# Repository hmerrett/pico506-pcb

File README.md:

# Pico506 hardware — rev 1.0

A dedicated PCB for the Pico506 ST-506/MFM/RLL hard drive emulator: two-layer,
138 × 74 mm, all through-hole, with real card-edge tabs so it plugs into a
period ST-506 control/data cable pair the same way an ST-225 does.

**This repository is the board only.** The emulator itself — the RP2040 firmware,
the PIO signal generation, the SD card image format, and the explanation of how
any of it works — is Kuba Szczodrzyński's
[**kuba2k2/pico506**](https://github.com/kuba2k2/pico506). Read that first; this
board is useless without it. Kuba's write-up
[*Emulating a 1987 proprietary RLL hard drive*](https://kuba.szczodrzynski.pl/posts/toshiba-t1200/rll-hdd-emulator/)
is the long-form story of the project and the reference for the interface
behaviour this layout is built around.

This file covers the board: what to buy, how to strap it, and what to tell
the fab. See [Credits](#credits) for what is original here and what is not.

> **Status:** schematic and layout are complete and clean — ERC 0, DRC 0 at
> `--severity-all` (see [`erc.txt`](erc.txt), [`drc.txt`](drc.txt)).
> **It has not been fabricated or brought up yet.** Nothing here has been
> validated against real hardware; treat rev 1.0 as a first spin.

| Front | Back |
|---|---|
|  |  |

Also in [`doc/`](doc/): an isometric render, front/back layer PDFs, gerbers +
Excellon (`pico506-gerbers.zip`), a CSV BOM and a placement file. The schematic
PDF is [`pico506-sch.pdf`](pico506-sch.pdf).

## Bill of materials

36 line items, 62 parts, nothing surface-mount and nothing exotic. Quantities
and designators below are generated from the schematic — the machine-readable
copy is [`doc/pico506-bom.csv`](doc/pico506-bom.csv).

### Semiconductors

| Ref | Qty | Value | Notes |
|---|---|---|---|
| U1 | 1 | Raspberry Pi Pico | Pico or Pico W, THT header or castellated. The footprint takes either. |
| U2, U3 | 2 | 74LS05 | Hex inverter, **open collector**. Not 7404 — the open-collector output is what lets the terminated 5 V bus idle high. |
| U4, U5 | 2 | 7438 | Quad NAND, **open collector**, buffered. Plain `7438` (or `74S38`) is preferred over `74LS38`: the LS part sinks 24 mA where the bus wants 40 mA to hold a 220/330-terminated line at a valid low. 74LS38 will usually work with one drive on a short cable; use 7438 if you want spec margin. |
| U6 | 1 | AM26LS31CN | Quad RS-422 differential **driver** (READ data out). |
| U7 | 1 | MC3486N | Quad RS-422 differential **receiver** (WRITE data in). **AM26LS32AC** is a drop-in alternative and is usually easier to find. |
| Q1 | 1 | 2N3904 | LED sink for the front-panel activity LED. Any small NPN. |
| D1 | 1 | 1N5817 | Schottky, feeds the Pico's VSYS from +5 V. A 1N5819 or SS14-class part is fine; don't substitute a plain 1N400x — the forward drop leaves too little VSYS headroom. |
| D2 | 1 | LED 5 mm amber | `ACT` — activity. |
| D3 | 1 | LED 5 mm green | `PWR` — power. |

### Passives

| Ref | Qty | Value | Notes |
|---|---|---|---|
| RN1 | 1 | 220 Ω SIP-9 | Terminator pull-up half. **Bourns 4609X-101-221** (bussed, 8 resistors, common pin 1). Fit in a 9-pin SIP socket — see [Termination](#termination). |
| RN2 | 1 | 330 Ω SIP-9 | Terminator pull-down half. **Bourns 4609X-101-331**. Also socketed. |
| R21 | 1 | 220 Ω | Fixed 220/330 divider on the *selected* drive-select line, after the J4 jumper — the way an ST-225 does it. Not removable. |
| R22 | 1 | 330 Ω | ” |
| R1–R9, R16 | 10 | 1 kΩ | R1–R9 pull the 74LS05 open-collector outputs up to +3V3 for the Pico. R16 is the PWR LED resistor. |
| R10, R14, R15 | 3 | 470 Ω | R10 is the WRITE FAULT input pull-up; R14/R15 are the ACT LED resistors (on-board and front-panel). |
| R11, R12 | 2 | 100 Ω | R11 buzzer series, R12 terminates the WRITE differential pair across U7's inputs. |
| R13 | 1 | 4.7 kΩ | Q1 base. |
| R17–R20 | 4 | 10 kΩ | SD card SPI pull-ups. |
| C1 | 1 | 100 µF 16 V | Bulk on +5 V. Radial, 6.3 mm body, 2.5 mm pitch. |
| C2 | 1 | 22 µF 16 V | Bulk on VSYS. Radial, 5 mm body. |
| C3–C9 | 7 | 100 nF | Ceramic disc, 5 mm pitch. One per logic IC (C3–C8) plus one for the SD socket (C9). |
| C10 | 1 | 10 µF 16 V | +3V3 bulk next to the SD socket. |

All resistors are 1/4 W axial on a 10.16 mm (0.4 in) footprint — the classic
DIN0207 body with the leads bent out, so they lie flat.

### Connectors and mechanical

| Ref | Qty | Part | Notes |
|---|---|---|---|
| J1 | — | ST-506 control, 34-pin card edge | Etched into the board. Mates a 3M 3463 / AMP 88373-3 style IDC card-edge socket. |
| J2 | — | ST-506 data, 20-pin card edge | Etched into the board. Mates 3M 3461 / AMP 88373-6. |
| J3 | 1 | **AMP/TE 350211-1** 4-pos MATE-N-LOK | Cable side is **AMP 1-480424-0** with 350550-series pins. This is the standard 4-pin drive power connector. The footprint expects the vertical header with its legs formed 90° for rear entry — exactly what Seagate did — or use a right-angle MATE-N-LOK equivalent. |
| FG1 | 1 | **AMP 61761-2** faston tab | Frame ground, 0.187 in tab, 3.3 mm hole. Or just bolt a ring lug through it. |
| SD1 | 1 | **Hirose DM1AA-SF-PEJ(82)** | Full-size push-push SD socket. The card ejects over the board's front edge. |
| SW1 | 1 | 6 mm tactile switch, 4.3 mm | `RST` — pulls the Pico's RUN low. |
| J4 | 1 | 2×4 pin header, 2.54 mm | Drive select. See [Straps](#straps-and-jumpers). |
| J5 | 1 | 1×3 pin header | UART console: GND / TX / RX. |
| J6 | 1 | 1×2 pin header | `SERVO GATE` — 3.3 V logic, JVC RLL drives only. |
| J7 | 1 | 1×2 pin header | Front-panel activity LED: pin 1 anode, pin 2 cathode. |
| JP1 | 1 | 1×2 pin header | `WF EN` — WRITE FAULT enable. |
| TP1 | 1 | test pad | +12 V, so you can confirm the rail without probing the connector. |
| H1–H4 | 4 | M3 | 3.2 mm mounting holes. |
| — | 6 | DIP socket | 4 × DIP-14, 2 × DIP-16. Optional but recommended. |
| — | 2 | SIP-9 socket | For RN1/RN2, so the terminator can come out. **Not optional** if this drive might sit mid-chain. |

## Straps and jumpers

### J4 — drive select

The silkscreen reads `DS 4 3 2 1` left to right (west to east). Each column is
one J1 drive-select line on its odd pin and the shared `DS_SEL_N` node on its
even pin; fitting a shunt across one column selects that drive address.
**Fit exactly one shunt.**

| Column | J1 pin | Selects |
|---|---|---|
| `1` (east) | 26 | DS1 |
| `2` | 28 | DS2 |
| `3` | 30 | DS3 |
| `4` (west) | 32 | DS4 |

Which one you want depends on your controller's cable. With a straight-through
control cable, the first drive is DS1. With an **IBM-style twisted control
cable** the twist reassigns the select lines between the two drive connectors,
and the drive on the end (twisted) connector wants **DS2** — that is the
intended default for this board. Check your controller's manual: this is the
single most common reason an otherwise-working drive is not detected.

Downstream of the shunt, `DS_SEL_N` carries its own fixed 220/330 divider
(R21/R22), matching ST-225 practice — that termination stays fitted regardless
of chain position.

### Other headers

| Header | Fitted | Effect |
|---|---|---|
| JP1 `WF EN` | open (default) | WRITE FAULT is not driven; the line idles inactive via R10. |
| JP1 `WF EN` | closed | Firmware drives WRITE FAULT from GP22. Only close this if your firmware build actually asserts it. |
| J6 `SERVO GATE` | — | 3.3 V SERVO GATE for JVC JD-3824-class RLL drives. Leave unconnected for ordinary MFM. |
| J7 `FRONT LED` | — | Parallels the on-board ACT LED to a panel LED. Pin 1 is the anode. |
| J5 `UART` | — | Console at GND/TX/RX. 3.3 V logic — do not connect a 5 V TTL adapter. |

## Termination

ST-506 is a daisy chain, and the spec puts a 220 Ω/330 Ω divider on every
control input — but **only on the drive at the far end of the cable.** Every
other drive on the chain must have its terminator removed, or the lines are
loaded several times over and nothing reads reliably.

That is what RN1 (220 Ω) and RN2 (330 Ω) are, and it is why they belong in
sockets:

- **Last drive on the control cable** (or the only drive): RN1 and RN2 fitted.
- **Any other position:** pull both packs out.

The silkscreen says `TERM: LAST DRIVE ONLY` next to them as a reminder. The
data cable (J2) is point-to-point and needs no such choice — the WRITE pair's
terminator (R12) is soldered down.

## Connectors and keying

Both card-edge tabs stand 5 mm proud of the main outline, are 1.6 mm thick, and
carry a **0.914 mm key slot routed 12.5 mm in from the tab tip, between pins 4
and 6** — the standard ST-506 keying, so a connector cannot be seated
backwards. Odd pins are on the front (F.Cu) face, even pins on the back, at
2.54 mm pitch; fingers are 1.40 mm wide and 11.43 mm long with the copper
pulled back 0.45 mm from the routed tip.

### Relief cut-outs

The fingers are 11.43 mm long but the tab only stands 5 mm proud, so the board
is cut away **beside** each tab as well — otherwise the mating socket's shell
hits the main board edge after 5 mm with two thirds of the finger length still
unengaged. Each relief runs inboard to y = 67.57 mm, level with the finger
tops, giving a free-standing tongue exactly as long as the gold:

| Relief | Width | Note |
|---|---|---|
| J1 west | **5.34 mm** | Limited by the J3 power housing 0.6 mm further west, not by choice — see below. |
| J1 east | 6.00 mm | |
| J2 west | 6.00 mm | |
| J2 east | 2.90 mm | The board simply ends here; the whole south-east corner is removed, so there is nothing east of the J2 tab to foul. |

The overall envelope is unchanged — 138 × 74 mm plus the 5 mm tabs — so this
costs nothing mechanically.

> **Check this against your actual sockets.** The J1 relief can only be
> 5.34 mm wide on its west side, because the J3 power connector housing (a full
> 1.00 in wide, its east face at x = 25.62 mm) is immediately beyond it. If
> your J1 socket needs more than that, the obstruction is the *power connector
> body*, not the board, and the fix is to shift J3 east — which moves it off the
> measured ST-225 position. `TAB_RELIEF_W` in
> [`tools/layout.py`](tools/layout.py) is the single knob for relief width.

Extending the tabs further instead of notching would also work and is a
one-constant change (`TAB_PROTRUDE`), but it moves every finger pad south,
invalidates all the hand-routed finger escapes, and grows the board's depth
past the drive's rear plane.

Lateral positions follow the measured ST-225 arrangement so ordinary cable
dressing just works. Measured from the board's west edge:

| Tab | Centre | Width | Pins |
|---|---|---|---|
| J1 control | 54.10 mm | 45.09 mm | 34 |
| J2 data | 121.45 mm | 27.30 mm | 20 |

J1 uses the ST-506/412 control pinout (even pins signal, odd pins ground); J2
uses the ST-412 data pinout, with the two differential pairs on 13/14 (WRITE)
and 17/18 (READ). Both are enumerated in
[`tools/netlist.py`](tools/netlist.py), which is the single source of truth for
the whole design.

J3 power is the usual 4-pin order: **pin 1 = +12 V**, pins 2 and 3 ground,
**pin 4 = +5 V**, marked on the silkscreen. +12 V is not used by the emulator —
it is brought to TP1 only so you can verify the supply.

## Mechanical

Everything below is from [`tools/layout.py`](tools/layout.py); the origin is the
board's north-west corner viewed from the component side.

- **Main outline:** 138.0 × 74.0 mm, 1.6 mm FR4. The rear (south) edge is the
  drive's rear plane; the two card-edge tabs protrude 5 mm past it for cable
  access, with 1 mm 45° corner cuts at the tab tips. The board is notched
  beside each tab so the sockets can seat — see
  [Relief cut-outs](#relief-cut-outs). The south-east corner is cut away
  entirely as part of that.
- **Mounting holes** (3.2 mm, M3): H1 (5, 5), H2 (133, 5), H3 (5, 40),
  H4 (133, 52).
- **Frame ground** faston FG1 sits between the two tabs, 6 mm in from the rear
  edge at x = 93.5.
- **SD card** ejects over the *front* (north) edge — leave that edge clear in
  any enclosure.
- **USB** and the `RST` button are the other two things you will want access
  to: USB is at the Pico's west end, `RST` at the east edge.

If you are building an enclosure or a bay adapter: this board is not a
mechanical drop-in for a 3.5 in or 5.25 in drive. It reproduces the *electrical
and connector* geometry of an ST-225 rear face, not its chassis. On a real
drive the card-edge mid-plane sits roughly 4.8 mm above the bay floor; if you
want the cables to land where a drive's would, that is the dimension to match,
and SFF-8501 gives the bay hole pattern to mount against. The four holes here
are a generic rectangle, not the SFF pattern — pick them up with standoffs.

## Fab notes

Two layers, 1.6 mm FR4, 1 oz copper, minimum track 0.2 mm and minimum
clearance 0.18 mm — comfortably inside every cheap prototype service's
capability. Two things are *not* default, though, and both matter:

1. **Card-edge fingers need hard gold.** Selective ENIG or hard gold plating on
   the tabs, Ni ≥ 2.5 µm / Au ≥ 0.4 µm. HASL fingers will wear through and
   go intermittent. This is usually a paid option — say "gold fingers".
2. **Bevel the tabs, 30°, both faces, on both card edges.** Without the bevel
   the tabs are hard to insert and will chew the connector.

Also: the key slots are 0.914 mm routed slots cut right through, so the fab
needs to treat them as internal routing, not drills — as are the four relief
notches beside the tabs. All of it is on `Edge.Cuts`; the two plating notes are
written onto the `Cmts.User` layer of the board so they travel with the gerbers.

## Assembly order

Low parts first, and leave the socketed parts until you have tested the rails:

1. Diodes, resistors, resistor packs' sockets, IC sockets.
2. Ceramics, then electrolytics (watch polarity on C1/C2/C10 and D1's band).
3. Headers, SW1, SD socket, LEDs, buzzer, Q1.
4. J3 power and the FG1 faston.
5. **Before fitting any IC:** apply drive power and check +5 V, +3V3 (Pico
   fitted), +12 V at TP1, and that nothing is warm.
6. Fit the Pico, then the logic ICs, then RN1/RN2 if this is the last drive.
7. Set the J4 shunt for your controller's cable before first use.

## Regenerating the design

The schematic and board are **generated**, not hand-drawn —
[`tools/netlist.py`](tools/netlist.py) is the single source of truth and both
generators consume it. Do not edit the `.kicad_sch` or `.kicad_pcb` by hand;
your changes will be overwritten.

```bash
cd tools
python3 gen_sch.py ../pico506.kicad_sch   # schematic (+ writes sch_uuids.json)
python3 gen_footprints.py                 # project footprint library
./check.sh                                # board + zone fill + full DRC
./export.sh                               # renders, PDFs, gerbers, BOM
```

`check.sh` regenerates the board, fills the zones, re-stamps the `.kicad_pro`
(pcbnew's save clobbers it) and runs `--severity-all` DRC into
[`drc.txt`](drc.txt). It also surfaces the generators' own warnings — a
failed ground link or an unrouted net shows up there long before you notice it
as "unconnected items" in DRC.

Two analysis helpers, both needing KiCad's bundled python
(`/Applications/KiCad/KiCad.app/Contents/Frameworks/Python.framework/Versions/Current/bin/python3`):

- **`tools/stitch.py`** — walks the GND pour, unions every ground island with
  the tracks, vias and pads that touch it, and reports any fragment the main
  plane does not reach, along with a ready-to-paste fix (stitch via, bridge
  track, or a pad-to-pad link). This is how the ground plane got from six
  orphaned fragments — including floating IC ground pins — to a single
  connected plane. **Re-run it after any routing or placement change**: the
  coordinate-based entries in `GND_STITCH_VIAS` go stale as soon as the maze
  router lands differently, and a stale via can end up sitting on a signal
  track.
- **`tools/place_check.py`** — reports courtyard boxes and how deeply
  overlapping pairs interpenetrate, so a placement nudge can be sized instead
  of guessed.

### Things that will bite you

- **Some ground pads cannot be rescued after routing.** The inter-DIP corridors
  seal once the signal router fills them, and several have no B.Cu pour beneath
  to via down to. Those rescues (`GND_STUBS` in `gen_pcb.py`) are routed *as
  first-class nets inside the router's search*, so a pass only counts if the
  signals and the ground links both fit. Moving one to a post-routing pass will
  silently strand a decoupling cap's ground.
- **`router.CLR` is 0.24 mm against a 0.18 mm rule.** The slack absorbs a
  route's closest approach between grid cells. Raising it to 0.25 leaves the
  U3/U4 corridor one track short of holding both the signals and C5's ground
  rescue; lowering it starts producing real clearance violations.
- **R10 must stay at x = 90.** The WRITE-FAULT riser threads between the +3V3
  trunk descent at x = 87.9 and R10's pad column; that gap is what fits.
- **Reference designators are placed automatically** (`place_references()` in
  `gen_pcb.py`), by trying positions around each part and taking the first that
  clears every mask aperture, all footprint silk, the board texts and the board
  edge. Don't hand-place them — adjust the candidate list instead.
- **`lib_footprint_mismatch` is set to `ignore`** in the project file. The board
  is regenerated from the libraries every build, so "the board copy has drifted
  from the library" cannot happen the way it can on a hand-edited board. KiCad
  flags U1 anyway; its pads, graphics, zones and attributes all compare
  identical, and the residual difference is bookkeeping that survives a pcbnew
  load/save round-trip. Every other rule is at its default severity.

Longer-form layout history and the routing plan are in
[`tools/ROUTING_PLAN.md`](tools/ROUTING_PLAN.md).

## Credits

The Pico506 emulator is by **Kuba Szczodrzyński** —
[kuba2k2/pico506](https://github.com/kuba2k2/pico506), described at length in
[*Emulating a 1987 proprietary RLL hard drive*](https://kuba.szczodrzynski.pl/posts/toshiba-t1200/rll-hdd-emulator/).
That project is the emulator: the firmware, the PIO signal generation, the
level-shifter/inverter circuit this board's logic section is a direct
descendant of, and the pin assignment the whole layout is wired to. Without it
there is nothing to put on a PCB.

What this repository adds is the board itself: the schematic capture, the
two-layer layout, the ST-506 card-edge tabs and their ST-225-derived geometry,
the project footprint library, and the Python generators in
[`tools/`](tools/) that produce all of it. Bugs in the board are mine, not
upstream's.

Also drawn on: the [ST-506/ST-412 interface](https://en.wikipedia.org/wiki/ST-506/ST-412)
pinouts and the 220/330 termination and drive-select conventions from Seagate's
ST-225 documentation, and the [HDD Clicker](https://www.vogons.org/viewtopic.php?t=90047)
for the buzzer idea that upstream implements.

## Licence

[GNU General Public License v3.0](LICENSE) — the same licence as upstream, so
the board and the firmware it exists to carry stay under the same terms.

Copyright © 2026 Henry Merrett (this PCB: schematic, layout, footprints and
generators).
Copyright © 2025 Kuba Szczodrzyński (Pico506, from which this board's circuit
is derived).

This is a hardware design under a software licence, which is how upstream is
licensed and therefore what a derivative here has to be. In practice: the
design files are the "source", and if you fabricate, modify or distribute the
board you owe the recipients those files under the GPL. There is no warranty,
and note that **rev 1.0 has never been fabricated** — see the status note at
the top.

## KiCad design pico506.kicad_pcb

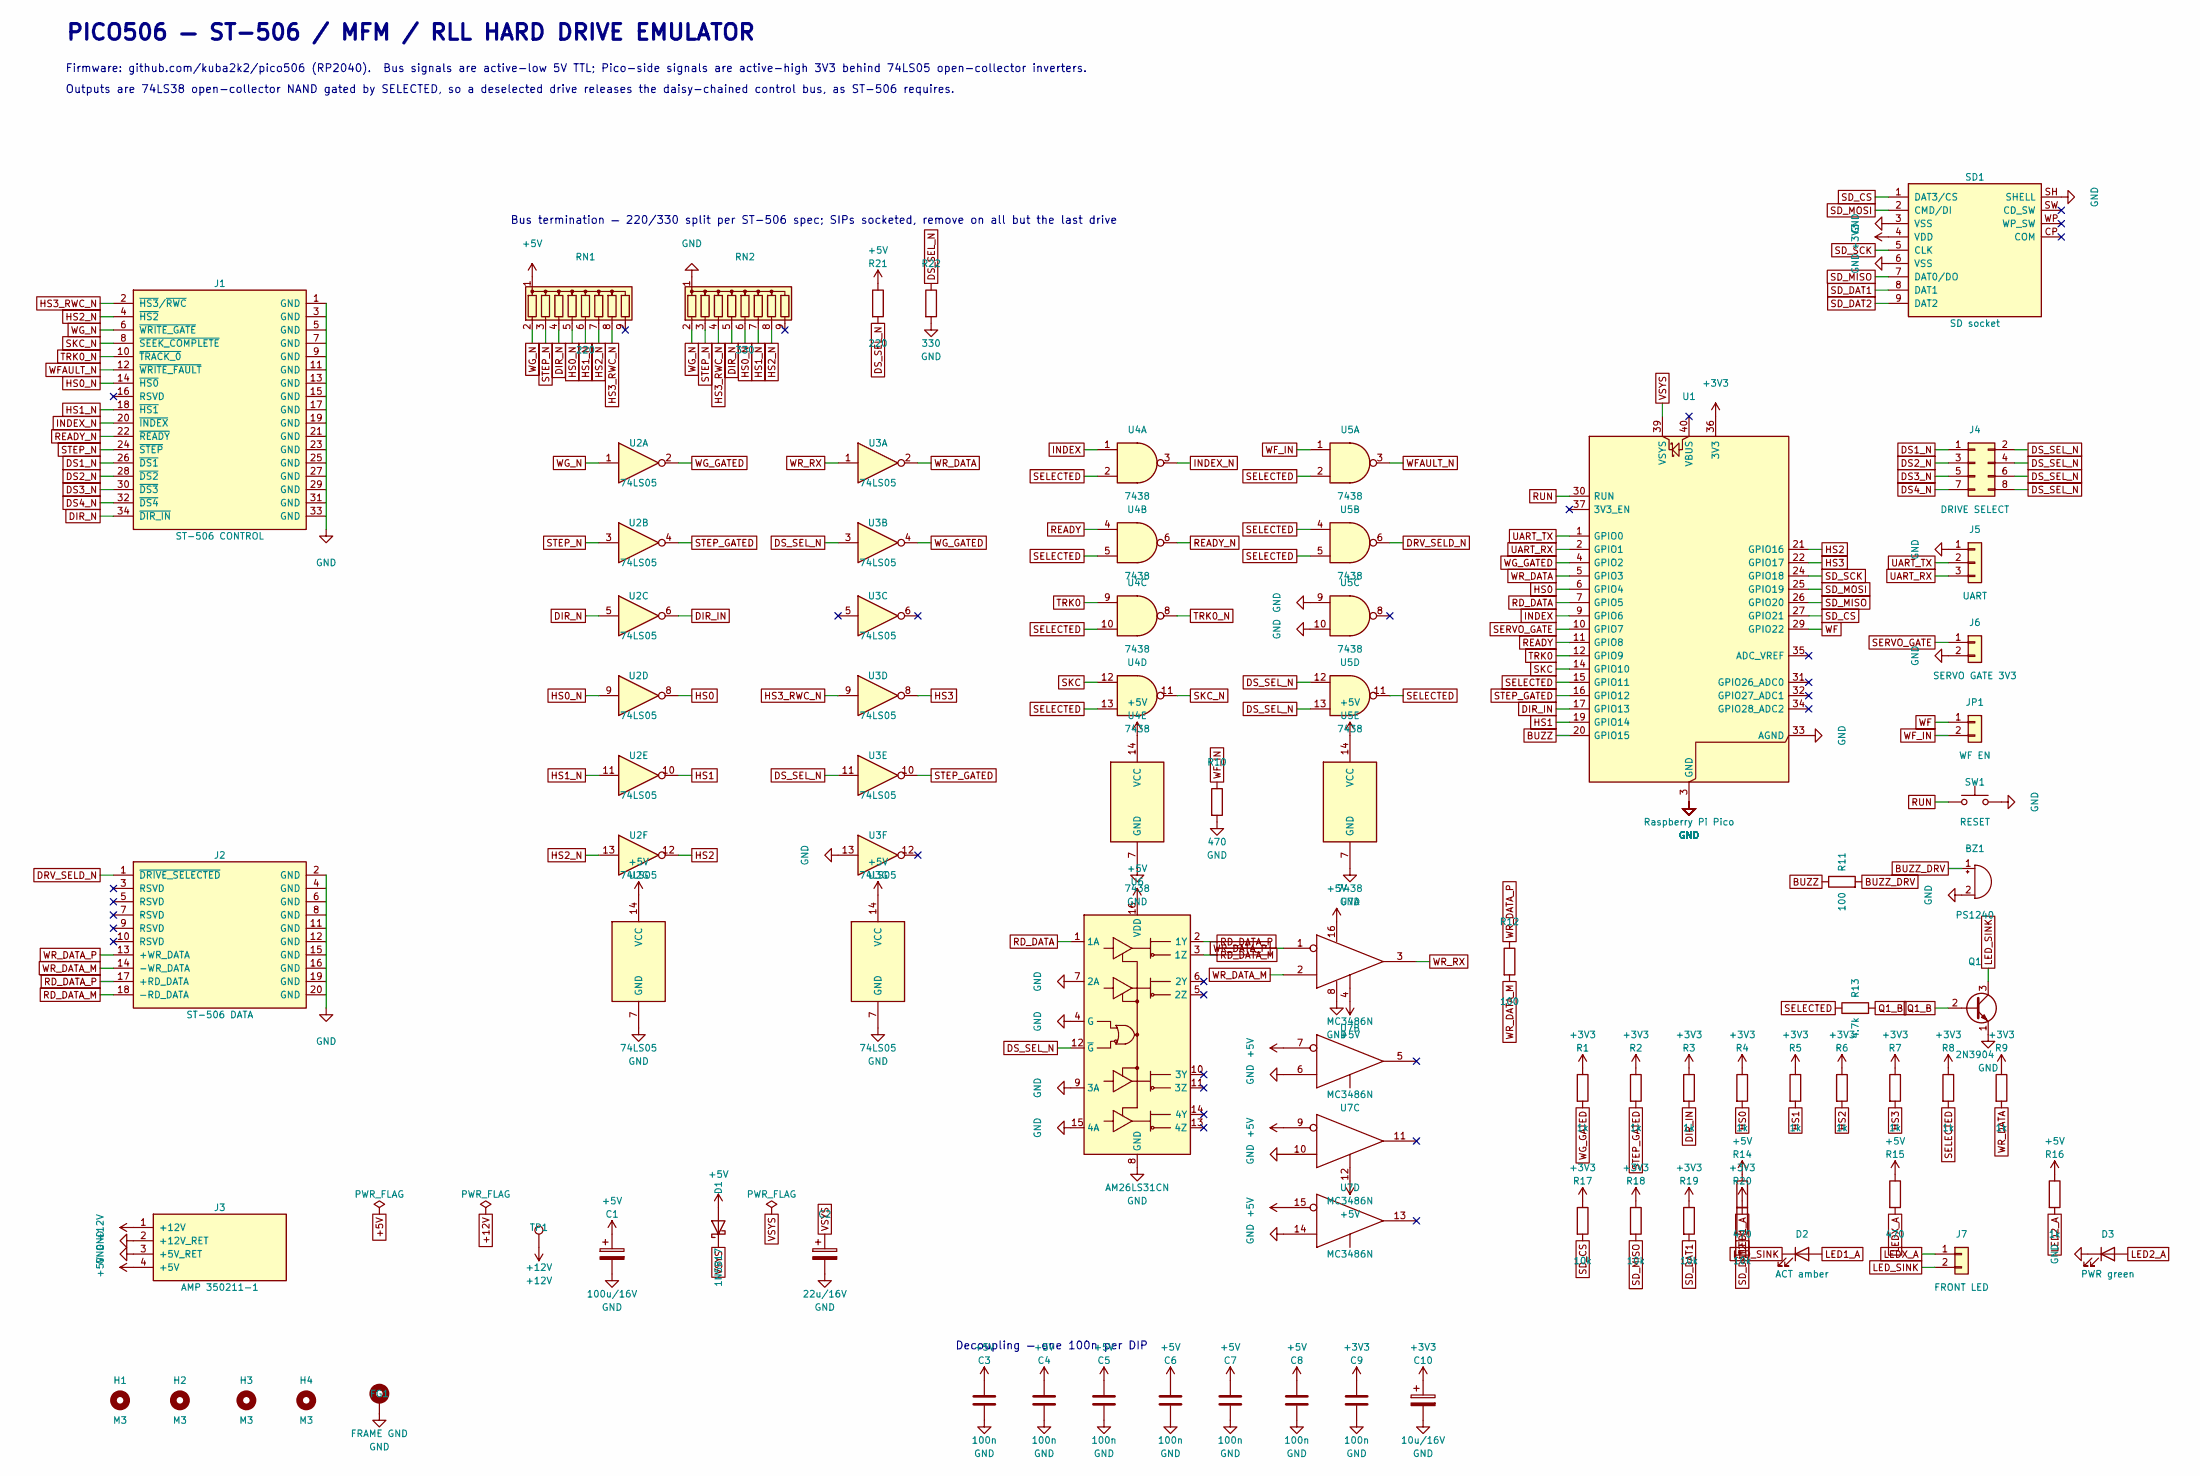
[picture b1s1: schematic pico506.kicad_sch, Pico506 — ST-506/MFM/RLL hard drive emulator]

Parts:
BZ1: PS1240; Buzzer_TDK_PS1240P02BT_D12.2mm_H6.5mm
C1: 100u/16V; CP_Radial_D6.3mm_P2.50mm
C2: 22u/16V; CP_Radial_D5.0mm_P2.50mm
C3, C4, C5, C6, C7, C8, C9: 100n; C_Disc_D5.0mm_W2.5mm_P5.00mm
C10: 10u/16V; CP_Radial_D5.0mm_P2.50mm
D1: 1N5817; D_DO-41_SOD81_P10.16mm_Horizontal
D2: ACT amber; LED_D5.0mm
D3: PWR green; LED_D5.0mm
FG1: FRAME GND; Faston_Tab_AMP61761
H1, H2, H3, H4: M3; MountingHole_3.2mm_M3
J1: ST-506 CONTROL; EdgeConn_ST506_J1_34
J2: ST-506 DATA; EdgeConn_ST506_J2_20
J3: AMP 350211-1; PWR_MATE-N-LOK_350211_Horizontal
J4: DRIVE SELECT; PinHeader_2x04_P2.54mm_Vertical
J5: UART; PinHeader_1x03_P2.54mm_Vertical
J6: SERVO GATE 3V3; PinHeader_1x02_P2.54mm_Vertical
J7: FRONT LED; PinHeader_1x02_P2.54mm_Vertical
JP1: WF EN; PinHeader_1x02_P2.54mm_Vertical
Q1: 2N3904; TO-92_Inline
R1, R2, R3, R4, R5, R6, R7, R8, R9, R16: 1k; R_Axial_DIN0207_L6.3mm_D2.5mm_P10.16mm_Horizontal
R10, R14, R15: 470; R_Axial_DIN0207_L6.3mm_D2.5mm_P10.16mm_Horizontal
R11, R12: 100; R_Axial_DIN0207_L6.3mm_D2.5mm_P10.16mm_Horizontal
R13: 4.7k; R_Axial_DIN0207_L6.3mm_D2.5mm_P10.16mm_Horizontal
R17, R18, R19, R20: 10k; R_Axial_DIN0207_L6.3mm_D2.5mm_P10.16mm_Horizontal
R21: 220; R_Axial_DIN0207_L6.3mm_D2.5mm_P10.16mm_Horizontal
R22: 330; R_Axial_DIN0207_L6.3mm_D2.5mm_P10.16mm_Horizontal
RN1: 220; R_Array_SIP9
RN2: 330; R_Array_SIP9
SD1: SD socket; SD_Hirose_DM1AA_SF_PEJ82
SW1: RESET; SW_PUSH_6mm_H4.3mm
TP1: +12V; TestPoint_Pad_D2.0mm
U1: Raspberry Pi Pico; RaspberryPi_Pico_Common_THT
U2, U3: 74LS05; DIP-14_W7.62mm
U4, U5: 7438; DIP-14_W7.62mm
U6: AM26LS31CN; DIP-16_W7.62mm
U7: MC3486N; DIP-16_W7.62mm

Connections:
+3V3: C9.1, C10.1, R1.1, R2.1, R3.1, R4.1, R5.1, R6.1, R7.1, R8.1, R9.1, R17.1, R18.1, R19.1, R20.1, SD1.4 (VDD), U1.36 (3V3)
+5V: C1.1, C3.1, C4.1, C5.1, C6.1, C7.1, C8.1, D1.2 (A), J3.4 (+5V), R14.1, R15.1, R16.1, R21.1, RN1.1 (common), U2.14 (VCC), U3.14 (VCC), U4.14 (VCC), U5.14 (VCC), U6.16 (VDD), U7.4 (ENABLE), U7.7 (E-), U7.9 (E-), U7.12 (ENABLE), U7.15 (E-), U7.16 (VCC)
+12V: J3.1 (+12V), TP1.1
BUZZ: R11.1, U1.20 (GPIO15)
BUZZ_DRV: BZ1.1 (+), R11.2
DIR_IN: R3.2, U1.17 (GPIO13), U2.6
DIR_N: J1.34 (~DIR_IN), RN1.4 (R3), RN2.5 (R4), U2.5
DRV_SELD_N: J2.1 (~DRIVE_SELECTED), U5.6
DS1_N: J1.26 (~DS1), J4.1
DS2_N: J1.28 (~DS2), J4.3
DS3_N: J1.30 (~DS3), J4.5
DS4_N: J1.32 (~DS4), J4.7
DS_SEL_N: J4.2, J4.4, J4.6, J4.8, R21.2, R22.1, U3.3, U3.11, U5.12, U5.13, U6.12 (~G)
GND: BZ1.2 (-), C1.2, C2.2, C3.2, C4.2, C5.2, C6.2, C7.2, C8.2, C9.2, C10.2, D3.1 (K), FG1.1, J1.1 (GND), J1.3 (GND), J1.5 (GND), J1.7 (GND), J1.9 (GND), J1.11 (GND), J1.13 (GND), J1.15 (GND), J1.17 (GND), J1.19 (GND), J1.21 (GND), J1.23 (GND), J1.25 (GND), J1.27 (GND), J1.29 (GND), J1.31 (GND), J1.33 (GND), J2.2 (GND), J2.4 (GND), J2.6 (GND), J2.8 (GND), J2.11 (GND), J2.12 (GND), J2.15 (GND), J2.16 (GND), J2.19 (GND), J2.20 (GND), J3.2 (+12V_RET), J3.3 (+5V_RET), J5.1, J6.2, Q1.1 (E), R10.2, R22.2, RN2.1 (common), SD1.3 (VSS), SD1.6 (VSS), SD1.SH (SHELL), SW1.2, U1.3 (GND), U1.8 (GND), U1.13 (GND), U1.18 (GND), U1.23 (GND), U1.28 (GND), U1.33 (AGND), U1.38 (GND), U2.7 (GND), U3.7 (GND), U3.13, U4.7 (GND), U5.7 (GND), U5.9, U5.10, U6.4 (G), U6.7 (2A), U6.8 (GND), U6.9 (3A), U6.15 (4A), U7.6 (E+), U7.8 (GND), U7.10 (E+), U7.14 (E+)
HS0: R4.2, U1.6 (GPIO4), U2.8
HS0_N: J1.14 (~HS0), RN1.5 (R4), RN2.6 (R5), U2.9
HS1: R5.2, U1.19 (GPIO14), U2.10
HS1_N: J1.18 (~HS1), RN1.6 (R5), RN2.7 (R6), U2.11
HS2: R6.2, U1.21 (GPIO16), U2.12
HS2_N: J1.4 (~HS2), RN1.7 (R6), RN2.8 (R7), U2.13
HS3: R7.2, U1.22 (GPIO17), U3.8
HS3_RWC_N: J1.2 (~HS3/~RWC), RN1.8 (R7), RN2.4 (R3), U3.9
INDEX: U1.9 (GPIO6), U4.1
INDEX_N: J1.20 (~INDEX), U4.3
LED1_A: D2.2 (A), R14.2
LED2_A: D3.2 (A), R16.2
LEDX_A: J7.1, R15.2
LED_SINK: D2.1 (K), J7.2, Q1.3 (C)
Q1_B: Q1.2 (B), R13.2
RD_DATA: U1.7 (GPIO5), U6.1 (1A)
RD_DATA_M: J2.18 (-RD_DATA), U6.3 (1Z)
RD_DATA_P: J2.17 (+RD_DATA), U6.2 (1Y)
READY: U1.11 (GPIO8), U4.4
READY_N: J1.22 (~READY), U4.6
RUN: SW1.1, U1.30 (RUN)
SD_CS: R17.2, SD1.1 (DAT3/CS), U1.27 (GPIO21)
SD_DAT1: R19.2, SD1.8 (DAT1)
SD_DAT2: R20.2, SD1.9 (DAT2)
SD_MISO: R18.2, SD1.7 (DAT0/DO), U1.26 (GPIO20)
SD_MOSI: SD1.2 (CMD/DI), U1.25 (GPIO19)
SD_SCK: SD1.5 (CLK), U1.24 (GPIO18)
SELECTED: R8.2, R13.1, U1.15 (GPIO11), U4.2, U4.5, U4.10, U4.13, U5.2, U5.4, U5.5, U5.11
SERVO_GATE: J6.1, U1.10 (GPIO7)
SKC: U1.14 (GPIO10), U4.12
SKC_N: J1.8 (~SEEK_COMPLETE), U4.11
STEP_GATED: R2.2, U1.16 (GPIO12), U2.4, U3.10
STEP_N: J1.24 (~STEP), RN1.3 (R2), RN2.3 (R2), U2.3
TRK0: U1.12 (GPIO9), U4.9
TRK0_N: J1.10 (~TRACK_0), U4.8
UART_RX: J5.3, U1.2 (GPIO1)
UART_TX: J5.2, U1.1 (GPIO0)
VSYS: C2.1, D1.1 (K), U1.39 (VSYS)
WF: JP1.1, U1.29 (GPIO22)
WFAULT_N: J1.12 (~WRITE_FAULT), U5.3
WF_IN: JP1.2, R10.1, U5.1
WG_GATED: R1.2, U1.4 (GPIO2), U2.2, U3.4
WG_N: J1.6 (~WRITE_GATE), RN1.2 (R1), RN2.2 (R1), U2.1
WR_DATA: R9.2, U1.5 (GPIO3), U3.2
WR_DATA_M: J2.14 (-WR_DATA), R12.2, U7.2 (E+)
WR_DATA_P: J2.13 (+WR_DATA), R12.1, U7.1 (E-)
WR_RX: U3.1, U7.3 (OUT)

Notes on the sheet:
PICO506 — ST-506 / MFM / RLL HARD DRIVE EMULATOR
Firmware: github.com/kuba2k2/pico506 (RP2040). Bus signals are active-low 5V TTL; Pico-side signals are active-high 3V3 behind 74LS05 open-collector inverters.
Outputs are 74LS38 open-collector NAND gated by SELECTED, so a deselected drive releases the daisy-chained control bus, as ST-506 requires.
Bus termination — 220/330 split per ST-506 spec; SIPs socketed, remove on all but the last drive
Decoupling — one 100n per DIP

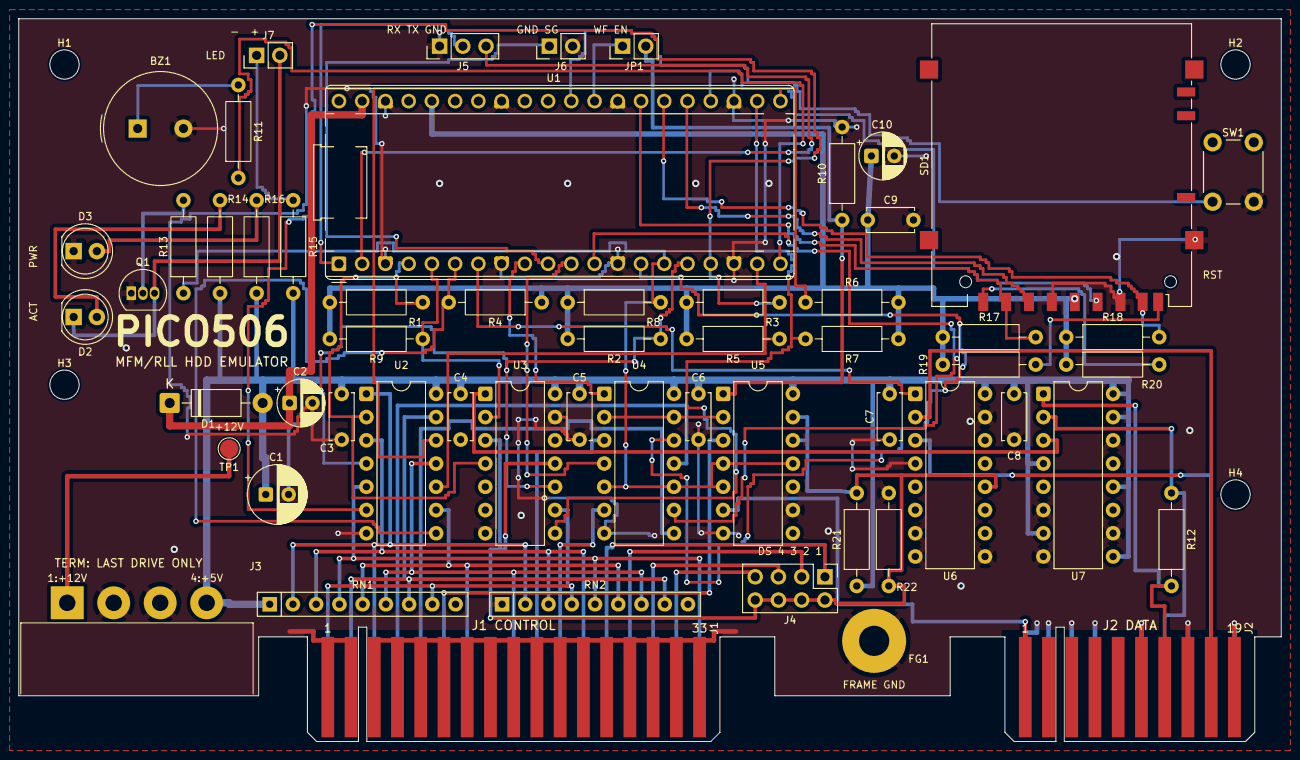
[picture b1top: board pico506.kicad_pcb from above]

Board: 2 copper layers, 138.0 x 79.0 mm, 62 parts (0 on the bottom side), 61 nets.

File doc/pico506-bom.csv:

"Refs","Value","Footprint","Qty","Datasheet"
"BZ1","PS1240","Buzzer_Beeper:Buzzer_TDK_PS1240P02BT_D12.2mm_H6.5mm","1",""
"C1","100u/16V","Capacitor_THT:CP_Radial_D6.3mm_P2.50mm","1",""
"C2","22u/16V","Capacitor_THT:CP_Radial_D5.0mm_P2.50mm","1",""
"C3-C9","100n","Capacitor_THT:C_Disc_D5.0mm_W2.5mm_P5.00mm","7",""
"C10","10u/16V","Capacitor_THT:CP_Radial_D5.0mm_P2.50mm","1",""
"D1","1N5817","Diode_THT:D_DO-41_SOD81_P10.16mm_Horizontal","1",""
"D2","ACT amber","LED_THT:LED_D5.0mm","1",""
"D3","PWR green","LED_THT:LED_D5.0mm","1",""
"FG1","FRAME GND","pico506-lib:Faston_Tab_AMP61761","1",""
"H1-H4","M3","MountingHole:MountingHole_3.2mm_M3","4",""
"J1","ST-506 CONTROL","pico506-lib:EdgeConn_ST506_J1_34","1",""
"J2","ST-506 DATA","pico506-lib:EdgeConn_ST506_J2_20","1",""
"J3","AMP 350211-1","pico506-lib:PWR_MATE-N-LOK_350211_Horizontal","1",""
"J4","DRIVE SELECT","Connector_PinHeader_2.54mm:PinHeader_2x04_P2.54mm_Vertical","1",""
"J5","UART","Connector_PinHeader_2.54mm:PinHeader_1x03_P2.54mm_Vertical","1",""
"J6","SERVO GATE 3V3","Connector_PinHeader_2.54mm:PinHeader_1x02_P2.54mm_Vertical","1",""
"J7","FRONT LED","Connector_PinHeader_2.54mm:PinHeader_1x02_P2.54mm_Vertical","1",""
"JP1","WF EN","Connector_PinHeader_2.54mm:PinHeader_1x02_P2.54mm_Vertical","1",""
"Q1","2N3904","Package_TO_SOT_THT:TO-92_Inline","1",""
"R1-R9,R16","1k","Resistor_THT:R_Axial_DIN0207_L6.3mm_D2.5mm_P10.16mm_Horizontal","10",""
"R10,R14,R15","470","Resistor_THT:R_Axial_DIN0207_L6.3mm_D2.5mm_P10.16mm_Horizontal","3",""
"R11,R12","100","Resistor_THT:R_Axial_DIN0207_L6.3mm_D2.5mm_P10.16mm_Horizontal","2",""
"R13","4.7k","Resistor_THT:R_Axial_DIN0207_L6.3mm_D2.5mm_P10.16mm_Horizontal","1",""
"R17-R20","10k","Resistor_THT:R_Axial_DIN0207_L6.3mm_D2.5mm_P10.16mm_Horizontal","4",""
"R21","220","Resistor_THT:R_Axial_DIN0207_L6.3mm_D2.5mm_P10.16mm_Horizontal","1",""
"R22","330","Resistor_THT:R_Axial_DIN0207_L6.3mm_D2.5mm_P10.16mm_Horizontal","1",""
"RN1","220","Resistor_THT:R_Array_SIP9","1",""
"RN2","330","Resistor_THT:R_Array_SIP9","1",""
"SD1","SD socket","pico506-lib:SD_Hirose_DM1AA_SF_PEJ82","1",""
"SW1","RESET","Button_Switch_THT:SW_PUSH_6mm_H4.3mm","1",""
"TP1","+12V","TestPoint:TestPoint_Pad_D2.0mm","1",""
"U1","Raspberry Pi Pico","pico506-lib:RaspberryPi_Pico_Common_THT","1",""
"U2,U3","74LS05","Package_DIP:DIP-14_W7.62mm","2",""
"U4,U5","7438","Package_DIP:DIP-14_W7.62mm","2",""
"U6","AM26LS31CN","Package_DIP:DIP-16_W7.62mm","1",""
"U7","MC3486N","Package_DIP:DIP-16_W7.62mm","1",""

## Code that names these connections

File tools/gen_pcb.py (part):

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

def routes_power():
    """+5V spine (B.Cu y39.5), +3V3 trunk (B.Cu y29.45), VSYS (F), +12V (F)."""
    W5, W3 = 0.8, 0.6
    # ---- +5V ----
    # feed riser from J3.4 up to the spine, and west along y64 to RN1.1
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            via(xv, sy, net, **V)
            route(net, [(xv, sy), (xv, uy), (ux, uy)], "B.Cu")

    # drive select lines: J4 columns run DS4..DS1 west->east (pin 1 east),
    # so the south-going stubs nest without crossing shallower slots
    DS = [
        ("DS4_N", 60.5,  jx("J1", 32), P("J4", 7), None),
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                  (81.6, 29.0), (80.72, 29.0), P("U1", 19)], "F.Cu", 0.3)
    route("HS1", [(81.6, 35.0), P("R5", 2)], "F.Cu", 0.3)

    # SELECTED: GP11/R8.2 node, link over the +5V spine on F, mid-gap trunk
    # between the U4 columns, row taps straight through to U5
    n = "SELECTED"
    route(n, [P("U1", 15), (69.29, 26.78), (69.29, 31.0), P("R8", 2)],
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    route(n, [P("U1", 6), (47.7, 28.5), (47.0, 28.5), P("R4", 2)],
          "F.Cu", 0.3)

    # WR_DATA: GP3 drop into R9.2, then B under the west walls, hopping to
    # F for the U3.2 entry (SKC's B lane blocks a straight climb)
    n = "WR_DATA"
    route(n, [P("U1", 5), (45.16, 28.5), (45.75, 28.5), (45.75, 33.2),
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

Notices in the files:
pico506.kicad_sch:
Firmware: github.com/kuba2k2/pico506 (c) 2025 Kuba Szczodrzynski
Licensed GPL-3.0-or-later. Design files: see Board above.
